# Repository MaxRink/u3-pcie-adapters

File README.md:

# U.3 PCIe adapters

Passive, PCIe 4.0 adapters for U.3 (SFF-TA-1001) NVMe drives, built around HPE P50230-B21 /
Samsung PM1735a drives that refuse U.2-wired hosts. KiCad projects, fabbed at JLCPCB or PCBWay.

## Designs

| Design | Boards | Status |
| --- | --- | --- |
| [**x16 / x8 U.3 cards**](designs/x16-u3-card/) | x8 card (2 drives), x16 card (4 drives, passive or with retimer), OCuLink cage board | cage board routed and DRC clean; cards in layout |
| [**Minisforum MS-01 / MS-A2**](designs/minisforum-u3/) | U.3-wired x4 card for the PCIe slot, U.3-wired replacement for the M.2 adapter | waiting on measurements of the stock adapters |
| [**Cooling shroud**](docs/thermal/) | 3D-printed high-temp shroud for the Jonsbo N5 | sized from the thermal analysis; model in progress |

<table>
<tr>
<td><br>Cage board, top</td>
<td><br>Cage board, bottom (OCuLink)</td>
</tr>
<tr>
<td><br>x8 card with 2 drives</td>
<td><br>x16 card with 4 drives</td>
</tr>
<tr>
<td><br>CFD: 4 drives x 25 W in line, 30 CFM</td>
<td><br>Hottest drive vs airflow (x8 / x16)</td>
</tr>
</table>

## Cooling in one paragraph

Each drive can draw ~25 W, and on the cards the drives sit in a row, so the air passes them one
after another. With 35 °C air coming in and a 70 °C case limit, the x8 card (2 drives) needs about
20 CFM and the x16 card (4 drives) about 30 CFM at ~150 Pa. That takes a 92x38 mm server-class
fan: it holds 2 drives at ~66 °C and 4 drives at ~71 °C (marginal; 3 mm shroud gaps or a 20 W
drive power state give margin). A 92x25 mm fan is not enough for either. Details, OpenFOAM
results and the calibrated model: [`docs/thermal/`](docs/thermal/).

## Layout

| Path | Contents |
| --- | --- |
| [`design-rules/`](design-rules/) | Shared PCIe 4.0 + JLCPCB/PCBWay rules: stackups, impedance, `.kicad_dru` DRC rules, KiCad starter templates, SI scripts |
| [`designs/x16-u3-card/`](designs/x16-u3-card/) | x16 / x8 slot cards for 2–4 U.3 drives, OCuLink cage board |
| [`designs/minisforum-u3/`](designs/minisforum-u3/) | U.3 adapters for Minisforum MS-01 / MS-A2 (PCIe x4 card, M.2-slot board) |
| [`tools/render/`](tools/render/) | Headless 3D renders of any `.kicad_pcb` (real copper/mask/silk, STEP parts, drives plugged in) |
| [`tools/thermal/`](tools/thermal/) | Analytical airflow/thermal model and OpenFOAM CFD case generator for the drive stack |
| [`docs/`](docs/) | Research notes, renders (`docs/img/`), thermal results (`docs/thermal/`) |

## Conventions

- One folder per design under `designs/`; one KiCad project per board inside it.
- Every board uses a template from `design-rules/templates/` and the custom rules in
  `design-rules/pcie4_jlc_pcbway.kicad_dru`. Change the rules there, not per board.
- Don't commit KiCad backups, `*.kicad_prl`, or fab output zips (see `.gitignore`);
  attach fab outputs to GitHub releases instead.
- Re-render a board after changing it (`tools/render/render.py`) so the README pictures match.

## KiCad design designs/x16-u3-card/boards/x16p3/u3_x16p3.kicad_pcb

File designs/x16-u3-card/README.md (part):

# U.3 adapter boards: x16 card, x8 card, OCuLink cage board

Passive PCIe 4.0 boards that carry true SFF-TA-1001 (U.3) wiring to 2.5" U.3 drives such as the
HPE P50230-B21 / Samsung PM1735a, which refuse U.2-wired hosts. Designed for a Jonsbo N5 build
with a 3D-printed cooling shroud.

## Boards

| Board | What it is | Status |
| --- | --- | --- |
| **x8 card** (`boards/x8/`) | x8 slot (x4x4 bifurcation), 2 drives on the card front (CEM component side), passive, REFCLK buffer, full sidebands, per-drive 12 V jumper and eFuse, 191.7 mm with the tail tab for the 6-pin | rev G routed, DRC clean; drive A 28–38 mm, drive B 45–66 mm (three lanes over the 50 mm rule); relies on PCIe lane reversal |
| **x16 card, passive, 4 drives** (`boards/x16p/`) | x16 slot (x4x4x4x4), 4 drives in a row on the card front, 334.7 mm with the tail tab (longer than a full-length CEM card); drives A–C sit 5.7 mm higher than D so lanes 8–15 pass under them | rev G; A 37–46 mm, B 43–69 mm, C ~107–126 mm, D ~158–178 mm: C/D run at PCIe Gen3 (silk says so); relies on lane reversal |
| **x16 card, passive, 3 drives** (`boards/x16p3/`) | same card with drives A–C only, 261.7 mm; host bifurcation x4x4x4 or x8x4x4, lanes 12–15 unused | rev G routed, DRC clean; A 37–46 mm, B 44–69 mm, C 101–121 mm (Gen3) |
| **CDCDB400 clock versions** (`boards/*-cdcdb400/`) | cards with a TI CDCDB400 instead of the PI6CB33401 / 9DBL0442 buffer | x8: rev G. x16: **still rev F (drives on the back)**, not laid out for the front cards yet; see [`docs/part-options.md`](../../docs/part-options.md) |
| **x16 card with retimer** | as above, with a retimer on lanes 8–15 so all 4 drives stay compliant | planned (part search) |
| **OCuLink cage board** (`boards/cage/`) | OCuLink 4i (SFF-8611) to U.3 breakout for a drive in a printed cage; 12 V in on a PCIe 6-pin | rev B routed, DRC clean (review fixes applied; the cabled path still needs a host-card retimer for full compliance) |

Renders are regenerated from the KiCad files whenever a board changes (see
[`tools/render`](../../tools/render/)); boards still in layout get their renders when they are DRC clean.

## OCuLink cage board

Rev B. 56.5 x 37.65 mm, 6 layers (JLC06161H-3313), PCIe lanes on L1/L6 only. The OCuLink receptacle sits on the
bottom in the edge notch, the U.3 receptacle on top mates the drive at the upper edge, and a PCIe 6-pin
(Molex Mini-Fit Jr) brings 12 V through a 3 A PTC fuse; a SOT-89 LDO (MCP1703AT-3302E/MB, pinout checked
against the Microchip datasheet; the HT7533-1 is an LCSC alternative only after its pinout is checked) makes 3.3 V aux. Four M3 slots (3.2 x 6.2 mm, along the insertion axis) hold it in
the printed cage.

Rev B changes (from the rev A review, `docs/reviews/cage-board-review.md`, and `docs/reviews/full-review-2026-11-13.md`):

- 220 nF AC caps on PER0/PER1 (bottom side, L5 voided under the pads). A U.3 drive has no TX caps on lanes 0/1
  (SFF-TA-1001 Rev 1.1 section 4.5), so rev A left those two lanes DC-coupled.
- The drive-side board edge now ends 9.4 mm from the peg line, 0.65 mm short of the housing face, so the board can
  no longer stop the drive before it is fully seated. The receptacle overhangs the edge by design.
- 100 k pull-down on PERST#: a missing or sideband-less cable holds the drive in reset.
- The four low-speed OCuLink vias moved off the PET via row into two rows in front of it, and a return via was
  added between the PET3 and PET2 transitions. The 11 mm slot in the L2/L5 planes is now two short ones with a
  2.7 mm bridge.
- Parts: F1 mSMD300-16V (3 A hold, C6851473), LED KT-0603YG (C2289), C3 50 V (C307331), LDO as above (the AMS1117
  was at its 15 V limit, needs a minimum load and is not stable with ceramic output caps).

The renders below still show rev A.

Still open on this board: the cabled path needs a retimer on the host card for full PCIe 4.0 compliance
(design-rules Rev E), PERST#/REFCLK/SMBus are not isolated when the cage is unpowered, and the PET0 lane is 30.4 mm
(0.4 mm over the per-board target).

| Top | Bottom (seen from below) |
| --- | --- |
|  |  |
|  |  |

With a 15 mm U.3 drive plugged in:

| Front | Back |
| --- | --- |
|  |  |

Copper, mask and silkscreen in the renders come from the real layer geometry. The U.3 and
OCuLink receptacles, the Mini-Fit header and the drive are simplified appearance models.

Fab files: [`fab/cage/`](fab/cage/) (Gerbers, BOM, CPL for JLCPCB / PCBWay).

## Rev G: drives on the card front

From rev G on the U.3 receptacles, the aux power plug, the fan header, the 12 V jumpers and every other tall part
sit on the card front (the CEM component side, where a card may be 14.47 mm tall and more with a free neighbour
slot). The back carries only flat SMD parts. Rev F and earlier had the drives on the back, where a CEM card may
only be 2.67 mm tall; those boards are in the git history (merge of PR #17).

| x8, drives fitted | x16 with 4 drives |
| --- | --- |
|  |  |

**Lane order.** Seen from the front, a receptacle's lane order runs against the finger order. The cards wire every
lane straight through, so finger lane n lands on drive lane 3 - n mod 4, and every x4 port has to train
lane-reversed. Lane reversal is optional in PCIe; most root ports and NVMe controllers do it, but it could not be
confirmed from any document for the EPYC 7002/7003 + Supermicro H12SSL + Samsung PM1735 combination this was
built for. **If neither end reverses, the drive does not link at all.** Check this with one drive before
populating the rest:

```
lspci -vv -s <drive's bus address> | grep -E "LnkCap|LnkSta"
# expected: LnkSta: Speed 16GT/s, Width x4   (drives C/D on the x16 cards: 8GT/s is by design)
```

A link at x1 or x2, or no device at all, means the port did not reverse. The rev F cards (drives on the back) are
the wiring that needs no reversal. Uncrossing the lanes on a front card is possible only by looping every lane
bundle around its receptacle (two signal layers, no room to cross): about 35 mm more per drive, which takes even
drive A out of the 50 mm budget. It is not built.

**How the cards are generated.** `gen/x8.py` and `gen/x16.py` build the card in a mirrored frame (drives on the
bottom, as before) and flip the whole board once when saving (`Kit.mirror_all`). Layer names in the generator are
mirrored too (L1 there is the physical L6, L3 the physical L4).

## x8 card

CEM x8 edge (bifurcate the slot x4x4). Two drives on the card front, the card is cut away behind them for airflow.
Drive A is next to the bracket (lanes 0–3, 28–38 mm), drive B at the free end (lanes 4–7, 45–66 mm; PET6, PET7 and
PER7 are over the 50 mm rule and have their own DRU rule, so expect drive B to be the first to drop to Gen3 on a
marginal host). The REFCLK buffer sits at the free end; the slot clock runs there on L4 under the lane field
(106 mm), drive A's pair comes back on the front layer under drive B. The PCIe 6-pin (J5), its bulk cap and TVS sit
on a 22.6 mm tail tab, plug toward the card end. The fan header is at the bracket end. AC caps (220 nF) sit on the
drive-to-host lanes per SFF-TA-1001. Sidebands and 12 V work as described under
[Sidebands and power](#sidebands-and-power). Fab files: [`fab/x8/`](fab/x8/).

## x16 card (passive)

Same construction with four drives in a row (D C B A from the free end, A at the bracket, 73 mm pitch). The 3-drive
card (`U3_DRIVES=3 python3 gen/x16.py`) is the same design without drive D. The drive at the free end sits on the
low peg line, the others 5.7 mm higher, so the lanes to the far drives pass between the fingers and the nearer
receptacles in a 0.9 mm-pitch stack. Lane lengths finger to receptacle: A 37–46 mm, B 43–69 mm, C 101–126 mm,
D 158–178 mm (the DRU documents the over-budget nets). C and D are past the Gen4 loss budget and are meant to run at
PCIe Gen3 (silk: "C/D: PCIe Gen3 only"). With the tail tab for the 6-pin the 4-drive card is 334.7 mm long, 22.6 mm
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
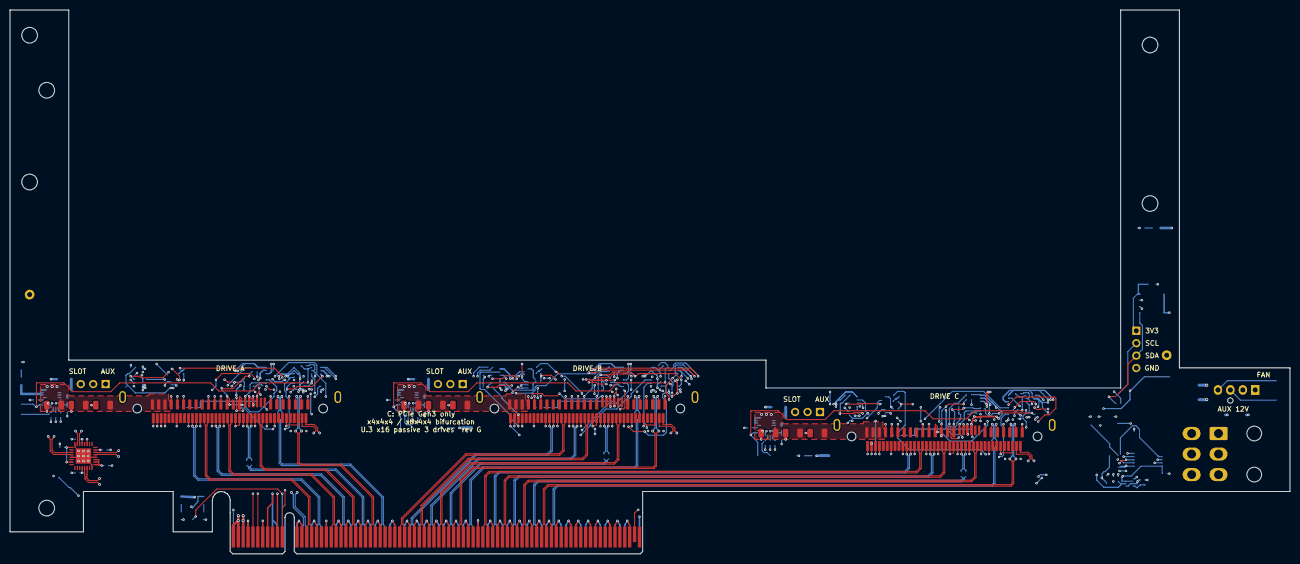
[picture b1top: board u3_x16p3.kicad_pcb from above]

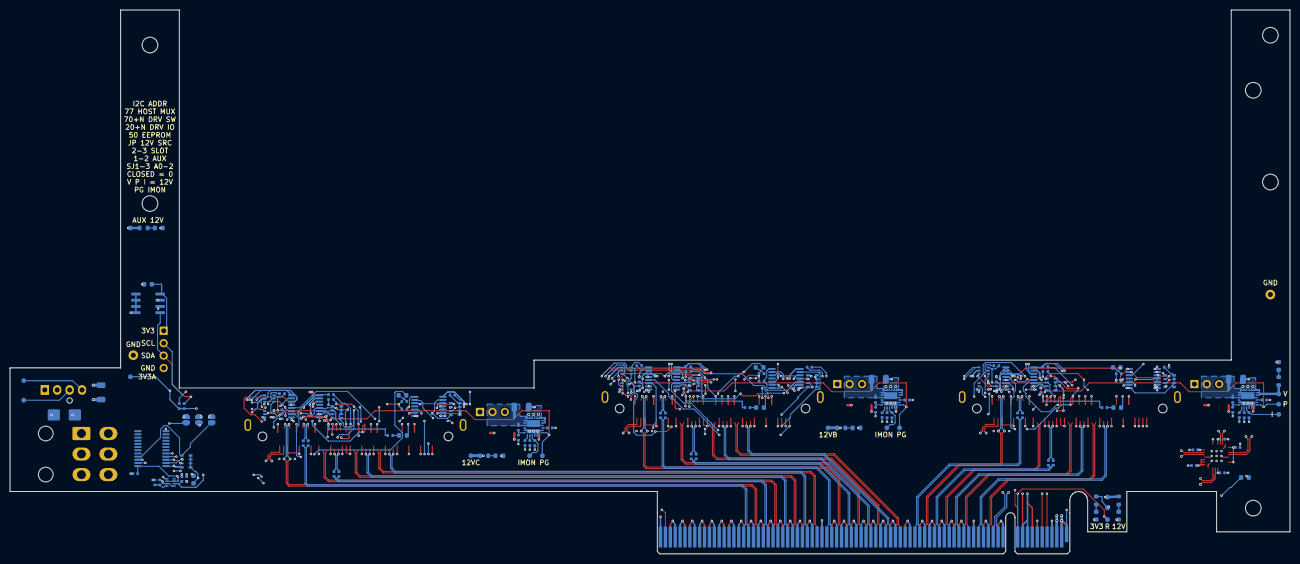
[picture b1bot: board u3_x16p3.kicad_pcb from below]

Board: 6 copper layers, 261.6 x 111.2 mm, 174 parts (152 on the bottom side), 170 nets.

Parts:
C1, C2, C3, C4, C5, C6, C7, C8, C20, C21, C22, C23, C30, C31, C32, C33, C40, C41, C42, C43: 100nF; C_0402_1005Metric
C9: 10uF; C_0603_1608Metric
C19, C24, C25, C34, C35, C44, C45: 22uF 25V X5R; C_1206_3216Metric
C26, C28, C36, C38, C46, C48: 10uF 50V X5R; C_1206_3216Metric
C27, C37, C47: 1nF; C_0402_1005Metric
C29, C39, C49: 4.7nF; C_0402_1005Metric
C90: 100nF; C_0603_1608Metric
C101, C102, C103, C104, C105, C106, C107, C108, C109, C110, C111, C112: 220nF 16V X7R; C_0402_1005Metric
D1, D2, D3, D40, D41, D42, D43, D44, D45: KT-0603YG; LED_0603_1608Metric
D10, D11, D12: XL-1608UYC-06 yellow (locate); LED_0603_1608Metric
D50: SMBJ15A; D_SMB
FB1: 600R@100MHz; L_0603_1608Metric
H1, H2: bracket; MountingHole_3.2mm_M3
H3, H4, H5, H6: M3 slot; MountingSlot_M3_3.2x6.2
H7, H8, H9, H10: M3; MountingHole_3.2mm_M3
J1: PCIe x16 edge; BUS_PCIexpress_x16
J5: PCIe 6-pin 45558-0003; Molex_Mini-Fit_Jr_5569-06A2_2x03_P4.20mm_Horizontal
J6: I2C local bus; PinHeader_1x04_P2.54mm_Vertical
J7: fan 4-pin PWM (fed from the aux 12 V plug); FanPinHeader_1x04_P2.54mm_Vertical
JA: PSAS4F2130021TR; Amphenol_PSAS4F213002_SFF-8639_U3_RA_SMD
JB: PSAS4F2130021TR; Amphenol_PSAS4F213002_SFF-8639_U3_RA_SMD
JC: PSAS4F2130021TR; Amphenol_PSAS4F213002_SFF-8639_U3_RA_SMD
JP1, JP2, JP3: PinHeader 1x03 2.54 mm THT: 2-3 SLOT (default), 1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; PinHeader_1x03_P2.54mm_Vertical
R1, R2: 4.7k; R_0402_1005Metric
R3, R26, R46, R66: 15k; R_0402_1005Metric
R4, R20, R21, R22, R23, R40, R41, R42, R43, R60, R61, R62, R63: 10k; R_0402_1005Metric
R11, R12, R13, R24, R28, R44, R48, R64, R68: 1k; R_0402_1005Metric
R25, R45, R65: 100k; R_0402_1005Metric
R27, R47, R67: 390R; R_0402_1005Metric
R90, R91, R93, R94, R95: 2.2k; R_0603_1608Metric
R92: 1k; R_0603_1608Metric
RN1, RN3, RN5: 4.7k x4; R_Array_Convex_4x0603
RN2, RN4, RN6, RN10: 10k x4; R_Array_Convex_4x0603
SJ1: A0 (close = 0); SolderJumper-2_P1.3mm_Open_RoundedPad1.0x1.5mm
SJ2: A1 (close = 0); SolderJumper-2_P1.3mm_Open_RoundedPad1.0x1.5mm
SJ3: A2 (close = 0); SolderJumper-2_P1.3mm_Open_RoundedPad1.0x1.5mm
TP1: 3V3_AUX; TestPoint_Pad_D1.0mm
TP2: 12V_AUX; TestPoint_Pad_D1.0mm
TP3: 12V; TestPoint_Pad_D1.0mm
TP4: 3V3; TestPoint_Pad_D1.0mm
TP5: PCIE_RST_N; TestPoint_Pad_D1.0mm
TP6: 12V_DRV_C; TestPoint_Pad_D1.0mm
TP7: IMON_C; TestPoint_Pad_D1.0mm
TP8: PG_C; TestPoint_Pad_D1.0mm
TP9: 12V_DRV_B; TestPoint_Pad_D1.0mm
TP10: IMON_B; TestPoint_Pad_D1.0mm
TP11: PG_B; TestPoint_Pad_D1.0mm
TP12: 12V_DRV_A; TestPoint_Pad_D1.0mm
TP13: PG_A; TestPoint_Pad_D1.0mm
TP14: IMON_A; TestPoint_Pad_D1.0mm
TP15: FAN_TACH; TestPoint_Pad_D1.0mm
TP16: FAN_PWM; TestPoint_Pad_D1.0mm
TP90, TP91: GND; TestPoint_Loop_D2.50mm_Drill1.0mm
U1: PI6CB33401ZHIEX; VQFN-32-1EP_5x5mm_P0.5mm_EP3.15x3.15mm
U2: TCA9548APWR; TSSOP-24_4.4x7.8mm_P0.65mm
U3: TPS2116DRLR; SOT-583-8
U4: AT24C02C-SSHM-T; SOIC-8_3.9x4.9mm_P1.27mm
U10, U14, U18: TCA9543APWR; TSSOP-14_4.4x5mm_P0.65mm
U11, U15, U19: TCA9554PWR; TSSOP-16_4.4x5mm_P0.65mm
U12, U16, U20: SN74LVC1G11DCKR; SOT-363_SC-70-6
U13, U17, U21: SN74LVC1G07DCKR; SOT-353_SC-70-5
U30, U31, U32: TPS259824ONRGER; TI_RGE0024M_VQFN-24_4x4mm_P0.5mm_SplitEP

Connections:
3V3: C3.2, C4.2, C5.1, C8.1, FB1.1, J1.A9, J1.A10, J1.B8, R3.2, R92.2, TP4.1, U1.9, U1.10, U1.11, U1.15, U1.19, U1.25, U1.31, U3.3, U3.5
3V3_A: C1.1, C2.1, FB1.2, U1.4, U1.21
3V3_AUX: C6.2, C9.1, C20.2, C21.2, C22.2, C23.1, C30.2, C31.2, C32.2, C33.1, C40.2, C41.2, C42.2, C43.1, C90.2, J6.1, JA.E3, JB.E3, JC.E3, R1.1, R2.1, R11.1, R12.1, R13.1, R21.1, R22.1, R23.1, R24.1, R41.1, R42.1, R43.1, R44.1, R61.1, R62.1, R63.1, R64.1, RN1.5, RN1.6, RN1.7, RN1.8, RN2.5, RN2.6, RN2.7, RN2.8, RN3.5, RN3.6, RN3.7, RN3.8, RN4.5, RN4.6, RN4.7, RN4.8, RN5.5, RN5.6, RN5.7, RN5.8, RN6.5, RN6.6, RN6.7, RN6.8, RN10.5, RN10.6, RN10.7, RN10.8, TP1.1, U2.24, U3.2, U3.7, U4.8, U10.14, U11.16, U12.5, U13.5, U14.1, U14.14, U15.1, U15.16, U16.5, U17.5, U18.2, U18.14, U19.2, U19.16, U20.5, U21.5
3V3_AUX_SLOT: C7.1, J1.B10, U3.6
12V: J1.A2, J1.A3, J1.B1, J1.B2, J1.B3, JP1.3, JP2.3, JP3.3, R91.2, TP3.1
12V_AUX: C19.1, D50.1, J5.1, J5.2, J5.3, J7.2, JP1.1, JP2.1, JP3.1, R90.1, TP2.1
12V_DRV_A: C24.2, C25.2, C26.2, JA.P13, JA.P14, JA.P15, R93.1, TP12.1, U30.17, U30.18, U30.19, U30.20, U30.21, U30.22, U30.23, U30.24
12V_DRV_B: C34.2, C35.2, C36.2, JB.P13, JB.P14, JB.P15, R94.1, TP9.1, U31.17, U31.18, U31.19, U31.20, U31.21, U31.22, U31.23, U31.24
12V_DRV_C: C44.2, C45.2, C46.2, JC.P13, JC.P14, JC.P15, R95.1, TP6.1, U32.17, U32.18, U32.19, U32.20, U32.21, U32.22, U32.23, U32.24
12V_SEL_A: C28.1, JP1.2, R25.2, U30.1, U30.2, U30.3, U30.16, U30.25
12V_SEL_B: C38.1, JP2.2, R45.2, U31.1, U31.2, U31.3, U31.16, U31.25
12V_SEL_C: C48.1, JP3.2, R65.2, U32.1, U32.2, U32.3, U32.16, U32.25
A_ACT_N: D1.1, JA.P11
A_LEDA: D1.2, R11.2
B_ACT_N: D2.1, JB.P11
B_LEDA: D2.2, R12.2
C_ACT_N: D3.1, JC.P11
C_LEDA: D3.2, R13.2
C_PER2_N: C101.2, JA.S12
C_PER2_P: C102.2, JA.S13
C_PER3_N: C103.2, JA.S5
C_PER3_P: C104.2, JA.S6
C_PER6_N: C105.2, JB.S12
C_PER6_P: C106.2, JB.S13
C_PER7_N: C107.2, JB.S5
C_PER7_P: C108.2, JB.S6
C_PER10_N: C109.2, JC.S12
C_PER10_P: C110.2, JC.S13
C_PER11_N: C111.2, JC.S5
C_PER11_P: C112.2, JC.S6
DPEN_A: JA.E25, U11.5
DPEN_B: JB.E25, U15.5
DPEN_C: JC.E25, U19.5
DRST_A: JA.E4, JA.E5, U12.4
DRST_B: JB.E4, JB.E5, U16.4
DRST_C: JC.E4, JC.E5, U20.4
DVDT_A: C27.1, U30.15
DVDT_B: C37.1, U31.15
DVDT_C: C47.1, U32.15
EN_A: R25.1, R26.2, U30.6
EN_B: R45.1, R46.2, U31.6
EN_C: R65.1, R66.2, U32.6
FAN_PWM: J7.4, TP16.1
FAN_TACH: J7.3, TP15.1
GND: C1.2, C2.2, C3.1, C4.1, C5.2, C6.1, C7.2, C8.2, C9.2, C19.2, C20.1, C21.1, C22.1, C23.2, C24.1, C25.1, C26.1, C27.2, C28.2, C29.1, C30.1, C31.1, C32.1, C33.2, C34.1, C35.1, C36.1, C37.2, C38.2, C39.1, C40.1, C41.1, C42.1, C43.2, C44.1, C45.1, C46.1, C47.2, C48.2, C49.1, C90.1, D40.1, D41.1, D42.1, D43.1, D44.1, D45.1, D50.2, J1.A4, J1.A12, J1.A15, J1.A18, J1.A20, J1.A23, J1.A24, J1.A27, J1.A28, J1.A31, J1.A34, J1.A37, J1.A38, J1.A41, J1.A42, J1.A45, J1.A46, J1.A49, J1.A51, J1.A54, J1.A55, J1.A58, J1.A59, J1.A62, J1.A63, J1.A66, J1.A67, J1.A70, J1.A71, J1.A74, J1.A75, J1.A78, J1.A79, J1.A82, J1.B4, J1.B7, J1.B12, J1.B13, J1.B16, J1.B18, J1.B21, J1.B22, J1.B25, J1.B26, J1.B29, J1.B32, J1.B35, J1.B36, J1.B39, J1.B40, J1.B43, J1.B44, J1.B47, J1.B49, J1.B52, J1.B53, J1.B56, J1.B57, J1.B60, J1.B61, J1.B64, J1.B65, J1.B68, J1.B69, J1.B72, J1.B73, J1.B76, J1.B77, J1.B80, J5.4, J5.5, J5.6, J6.4, J7.1, JA.E9, JA.E12, JA.E15, JA.E19, JA.E22, JA.MP, JA.P5, JA.P6, JA.P12, JA.S1, JA.S4, JA.S7, JA.S8, JA.S11, JA.S14, JA.S15, JA.S16, JA.S19, JA.S22, JA.S25, JA.S28, JB.E9, JB.E12, JB.E15, JB.E19, JB.E22, JB.MP, JB.P5, JB.P6, JB.P12, JB.S1, JB.S4, JB.S7, JB.S8, JB.S11, JB.S14, JB.S15, JB.S16, JB.S19, JB.S22, JB.S25, JB.S28, JC.E9, JC.E12, JC.E15, JC.E19, JC.E22, JC.MP, JC.P5, JC.P6, JC.P12, JC.S1, JC.S4, JC.S7, JC.S8, JC.S11, JC.S14, JC.S15, JC.S16, JC.S19, JC.S22, JC.S25, JC.S28, R4.2, R20.1, R26.1, R27.1, R28.1, R40.1, R46.1, R47.1, R48.1, R60.1, R66.1, R67.1, R68.1, SJ1.2, SJ2.2, SJ3.2, TP90.1, TP91.1, U1.8, U1.12, U1.24, U1.29, U1.33, U2.12, U3.1, U4.1, U4.2, U4.3, U4.4, U4.7, U10.1, U10.2, U10.7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
IFDET2_A: JA.E6, RN2.2, U11.11
IFDET2_B: JB.E6, RN4.2, U15.11
IFDET2_C: JC.E6, RN6.2, U19.11
IFDET_A: JA.P4, RN2.3, U11.10
IFDET_B: JB.P4, RN4.3, U15.10
IFDET_C: JC.P4, RN6.3, U19.10
ILIM_A: R27.2, U30.8
ILIM_B: R47.2, U31.8
ILIM_C: R67.2, U32.8
IMON_A: R28.2, TP14.1, U30.9
IMON_B: R48.2, TP10.1, U31.9
IMON_C: R68.2, TP7.1, U32.9
ITIMER_A: C29.2, U30.7
ITIMER_B: C39.2, U31.7
ITIMER_C: C49.2, U32.7
LEDA_3V3: D42.2, R92.1
LEDA_AUX: D40.2, R90.2
LEDA_DRV_A: D43.2, R93.2
LEDA_DRV_B: D44.2, R94.2
LEDA_DRV_C: D45.2, R95.2
LEDA_SLOT: D41.2, R91.1
LOCA_A: D10.2, R24.2
LOCA_B: D11.2, R44.2
LOCA_C: D12.2, R64.2
LOC_A: D10.1, U11.7
LOC_B: D11.1, U15.7
LOC_C: D12.1, U19.7
MUXA0: RN10.4, SJ1.1, U2.1
MUXA1: RN10.2, SJ2.1, U2.2
MUXA2: RN10.1, SJ3.1, U2.21
MUXCTL_A: R23.2, U10.3, U10.4, U10.8
MUXCTL_B: R43.2, U14.3, U14.4, U14.8
MUXCTL_C: R63.2, U18.3, U18.4, U18.8
MUX_RST_N: RN10.3, U2.3
PCIE_RST_N: J1.A11, TP5.1, U12.1, U16.1, U20.1
PCIE_WAKE_N: J1.B11, U13.4, U17.4, U21.4
PER0_N: J1.A17, JA.S26
PER0_P: J1.A16, JA.S27
PER1_N: J1.A22, JA.S20
PER1_P: J1.A21, JA.S21
PER2_N: C101.1, J1.A26
PER2_P: C102.1, J1.A25
PER3_N: C103.1, J1.A30
PER3_P: C104.1, J1.A29
PER4_N: J1.A36, JB.S26
PER4_P: J1.A35, JB.S27
PER5_N: J1.A40, JB.S20
PER5_P: J1.A39, JB.S21
PER6_N: C105.1, J1.A44
PER6_P: C106.1, J1.A43
PER7_N: C107.1, J1.A48
PER7_P: C108.1, J1.A47
PER8_N: J1.A53, JC.S26
PER8_P: J1.A52, JC.S27
PER9_N: J1.A57, JC.S20
PER9_P: J1.A56, JC.S21
PER10_N: C109.1, J1.A61
PER10_P: C110.1, J1.A60
PER11_N: C111.1, J1.A65
PER11_P: C112.1, J1.A64
PET0_N: J1.B15, JA.S23
PET0_P: J1.B14, JA.S24
PET1_N: J1.B20, JA.S17
PET1_P: J1.B19, JA.S18
PET2_N: J1.B24, JA.S9
PET2_P: J1.B23, JA.S10
PET3_N: J1.B28, JA.S2
PET3_P: J1.B27, JA.S3
PET4_N: J1.B34, JB.S23
PET4_P: J1.B33, JB.S24
PET5_N: J1.B38, JB.S17
PET5_P: J1.B37, JB.S18
PET6_N: J1.B42, JB.S9
PET6_P: J1.B41, JB.S10
PET7_N: J1.B46, JB.S2
PET7_P: J1.B45, JB.S3
PET8_N: J1.B51, JC.S23
PET8_P: J1.B50, JC.S24
PET9_N: J1.B55, JC.S17
PET9_P: J1.B54, JC.S18
PET10_N: J1.B59, JC.S9
PET10_P: J1.B58, JC.S10
PET11_N: J1.B63, JC.S2
PET11_P: J1.B62, JC.S3
PG_A: R22.2, TP13.1, U12.6, U30.13
PG_B: R42.2, TP11.1, U16.6, U31.13
PG_C: R62.2, TP8.1, U20.6, U32.13
PR1: R3.1, R4.1, U3.4
PRSNT_A: JA.P10, RN2.4, U11.9
PRSNT_B: JB.P10, RN4.4, U15.9
PRSNT_C: JC.P10, RN6.4, U19.9
PRSNT_N: J1.A1, J1.B81
PWRDIS_A: JA.P3, R20.2, U11.4
PWRDIS_B: JB.P3, R40.2, U15.4
PWRDIS_C: JC.P3, R60.2, U19.4
REFCLK_A_N: JA.E8, U1.28
REFCLK_A_P: JA.E7, U1.27
REFCLK_B_N: JB.E8, U1.23
REFCLK_B_P: JB.E7, U1.22
REFCLK_C_N: JC.E8, U1.14
REFCLK_C_P: JC.E7, U1.13
REFCLK_IN_N: J1.A14, U1.6
REFCLK_IN_P: J1.A13, U1.5
RSTEN_A: R21.2, U11.6, U12.3
RSTEN_B: R41.2, U15.6, U16.3
RSTEN_C: R61.2, U19.6, U20.3
SC1_A: RN1.1, U10.10
SC1_B: RN3.1, U14.10
SC1_C: RN5.1, U18.10
SD1_A: RN1.2, U10.9
SD1_B: RN3.2, U14.9
SD1_C: RN5.2, U18.9
SMBCLK_A: JA.E23, RN1.4, U10.6
SMBCLK_B: JB.E23, RN3.4, U14.6
SMBCLK_C: JC.E23, RN5.4, U18.6
SMBDAT_A: JA.E24, RN1.3, U10.5
SMBDAT_B: JB.E24, RN3.3, U14.5
SMBDAT_C: JC.E24, RN5.3, U18.5
SMCLK: J6.2, R1.2, U2.5, U4.6, U10.12, U11.14, U14.12, U15.14, U18.12, U19.14
SMCLK_SLOT: J1.B5, U2.22
SMDAT: J6.3, R2.2, U2.4, U4.5, U10.13, U11.15, U14.13, U15.15, U18.13, U19.15
SMDAT_SLOT: J1.B6, U2.23
WAKE_A: JA.P1, RN2.1, U11.12, U13.2
WAKE_B: JB.P1, RN4.1, U15.12, U17.2
WAKE_C: JC.P1, RN6.1, U19.12, U21.2

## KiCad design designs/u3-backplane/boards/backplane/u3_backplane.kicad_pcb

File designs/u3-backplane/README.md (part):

# Cabled U.3 backplane

A small NVMe backplane in the style of a Supermicro CSE-SAS-733TQ: U.3 drives stand on vertical receptacles,
every cable leaves sideways on the underside, and a host card in a PCIe x16 slot feeds it over SlimSAS 8i cables.
It is meant to sit flat in the top compartment of a Jonsbo N5 behind the two front 120 mm fans, with the drives
loaded from the top (so they can be swapped with the lid off), inside a printed cage.

| Board | Size | Drives | Cables | Files |
| --- | --- | --- | --- | --- |
| Backplane, 4 drives | 79.6 x 90.5 mm | 4 | 2 x SlimSAS 8i | `boards/backplane`, `fab/backplane` |
| Backplane, 6 drives | 119.6 x 90.5 mm (one 120 mm fan wide) | 6 | 3 x SlimSAS 8i | `boards/backplane6`, `fab/backplane6` |
| Host card, passive | 131 x 44 mm, PCIe x16 | 4 per card | 2 x SlimSAS 8i | `boards/host_passive`, `fab/host_passive` |

Two 6-drive modules side by side give 12 drives across both fans. That is 48 lanes: six 8i cables and three
x16 slots set to x4x4x4x4 (or a PCIe switch card).

All boards use the project's 6-layer rule set (JLC06161H-3313, 85 ohm pairs 0.157 / 0.152 mm, see
`design-rules/`). They are generated by the scripts in `gen/`; nothing is drawn by hand.

## Mechanics

Drawings: `docs/backplane_mech.svg`, `docs/backplane6_mech.svg`. Board-only STEP models are in `fab/*/`.

- Frame: seen from the drive side, origin top-left, x right, y down.
- Drive receptacles (Amphenol PSAS5F3130021TR, vertical, 8.15 mm tall) at x = 9.8 + 20 * i, y = 48.5, long axis
  along y, 20 mm pitch. Module pitch is 80 / 120 mm with 0.4 mm between boards.
- M3 holes: (3.2, 15.5), (W - 3.2, 15.5) and (36 + 40 * c, 86.3) for every drive pair c.
- Underside (all right angle, tallest part 13 mm, the cage keeps 15 mm clear):
  - y = 90.5 edge: one SlimSAS 8i per drive pair, centred at x = 15.8 + 40 * c.
  - y = 0 edge, left to right from the drive side: fan control in (1x4), 12 V in, 12 V out (Mini-Fit Jr 2x4),
    fan + fan control out (1x8).
- Slots between the drives let air through when the board stands upright. Lying flat they are not needed.

Assumed, not measured: the N5 top compartment has room for the cage (Max: "plenty of space"), and the drive's end
face sits about 6.5 mm above the board. The Amphenol drawing gives the 8.15 mm body height only.

## Electrical design

**Lanes.** One x4 link per drive, no lane crossings and exactly one via per net. Host transmit (PET) runs on L1
and drops to L6 behind the SlimSAS pads, drive transmit (PER) runs on L6. Lanes are 19 to 43 mm long. Pairs are
matched by the position of their vias, without serpentines (largest skew 0.004 mm, see
`fab/*/*-lengths.json`). 220 nF AC caps sit on the drive's lane 0 and 1 transmit pairs only
(SFF-TA-1001), S15 (HPT0) is grounded.

| SlimSAS connector | Port A (pins 1-18, host lanes 0-3) | Port B (pins 19-37, host lanes 4-7) |
| --- | --- | --- |
| first (left) | drive 1 | drive 0 |
| second | drive 3 | drive 2 |
| third (6-drive board) | drive 5 | drive 4 |

Sidebands follow SFF-9402: every port carries its own REFCLK, PERST#, CPRSNT#, CWAKE# and BP_TYPE (pulled low).
Cables must be the crossover type the spec describes (row A at one end is row B at the other).

**Power and hot plug.** 12 V enters on a PCIe 8-pin (Mini-Fit Jr) and is passed on to a second one for the next
module. Each drive has its own TPS259824 eFuse: about 3.9 A limit, soft start (10 nF on dV/dt), and it is only
switched on while a drive is present (PRSNT# or IfDet# low through a 74LVC1G00). A TPS3808 watches the drive's
12 V and releases the drive's PERST# about 125 ms after the rail is good, so a freshly inserted drive always sees
a proper reset. An empty bay is unpowered.

Daisy chain limit: a PCIe 8-pin is specified for 150 W. Four 25 W drives are 100 W, six are 150 W, so chain two
4-drive modules only with drives that stay under about 18 W each, and give every 6-drive module its own lead.

Host side of hot plug: the backplane is electrically safe to plug and pull. Whether the OS notices on its own
depends on the root port. A bifurcated consumer slot normally has no hot-plug slot capability, so use
`echo 1 > /sys/bus/pci/devices/<bdf>/remove` before pulling and `echo 1 > /sys/bus/pci/rescan` after inserting.
Boards that expose "PCIe hot plug" or Intel VMD for the slot handle it without that.

**Management.** One TCA9548A SMBus switch (address 0x71) gives every drive its own channel (channel = drive
number). One TCA9554 per drive pair (0x20, 0x21, 0x22) reads PRSNT#, IfDet#, IfDet2# and drives PWRDIS for both
drives (bits 0-3 even drive, 4-7 odd drive). The upstream bus is the 2-wire pair of port A on the first SlimSAS
connector; that port's PERST# also resets the switch. 3.3 V comes from an on-board LDO fed from 12 V (drive side,
above the fan header). L4 carries 12 V above the drives and to every eFuse and 3.3 V everywhere else.

**Fan.** The 1x8 header's pins 1-4 are a standard 4-pin fan header (GND, 12 V through a 1.1 A PTC, tach, PWM).
PWM and tach come from the "control in" header (mainboard fan header or the previous module), and PWM is passed
on by pins 5-8 to the next module. The 12 V pins of the control headers are not connected, so nothing is fed back
into the mainboard.

## Host card (passive)

PCIe x16 edge to two SlimSAS 8i, for a slot set to x4x4x4x4. The connectors sit on the underside at the top edge,
which keeps the lane order of the fingers. PET has one via, PER two. A 9DBL0442 buffer (bypass mode) gives each
port its own REFCLK, a TCA9546A (0x77) gives each port its own SMBus channel (channel 0 reaches the backplane's
switch), a TCA9554 (0x27) reads CPRSNT# and BP_TYPE of the four ports, PERST# goes to every port through 33 ohm
and the four CWAKE# lines join WAKE#. Trace length is 23 to 30 mm per lane.

A passive card plus a 0.5 m cable plus the backplane (19 to 43 mm) is past what PCIe 4.0 allows without
re-equalisation. Expect Gen3 to work and Gen4 to depend on the board and the cable. For Gen4, use a redriver or
retimer card.

**Redriver and retimer versions: not built (decided 2026-11-13).** For PCIe 4.0 a retimer card is bought instead
(see below). A redriver card (4 x DS160PR810) was analysed but not laid out: it does not re-time, so Gen4 over
0.5 m would stay uncertain. A retimer card cannot be laid out from public data, TI's public DS160PT801 datasheet
has no ball map.

## What to buy

Cables (one per drive pair): SlimSAS SFF-8654 8i to 8i, straight, 85 ohm, "PCIe 4.0", with sidebands, 0.5 m or
shorter.

| Cable | Notes |
| --- | --- |
| 3M 8ES8-1DF21-0.50 | reference-grade twinax, 85 ohm; the safest choice |
| 10Gtek CAB-8654/8654-8i-P-85 | "PCIe 4.0, 85 ohm, with sideband", 0.5 to 1 m, listed at about 15 USD (2026-11-13) |
| Delock 82303 (0.5 m) | SlimSAS 8i to 8i; impedance and sidebands not confirmed from the product page |

Avoid 100 ohm "SAS" cables and cables without sidebands: the drives would get no clock or reset.

Host card to buy instead of building one: a x16 to dual SlimSAS 8i **retimer** card, for example LR-LINK
LRNV9F24 or the C-Payne "SlimSAS PCIe gen4 host adapter x16" in its retimer version. Prices could not be read
from the vendor pages (LR-LINK sells on inquiry). Check before ordering that the card follows SFF-9402 on the
cable side (REFCLK and PERST# on every port); a card that only passes lanes will not bring up the drives.

## Cost estimate (JLCPCB, bare boards)

Not quoted live. Scaled from the project's quotes of 2026-11-13 for the same stackup (6 layers, ENIG, impedance
control, 0.2 mm vias: 141 to 188 USD for 5 to 10 cards of 190 to 310 mm length), where the fixed 6-layer charges
dominate:

| Board | 5 pcs | 10 pcs |
| --- | --- | --- |
| Backplane, 4 drives | about 105 USD | about 115 USD |
| Backplane, 6 drives | about 115 USD | about 130 USD |
| Host card (adds gold fingers and bevel) | about 125 USD | about 140 USD |

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
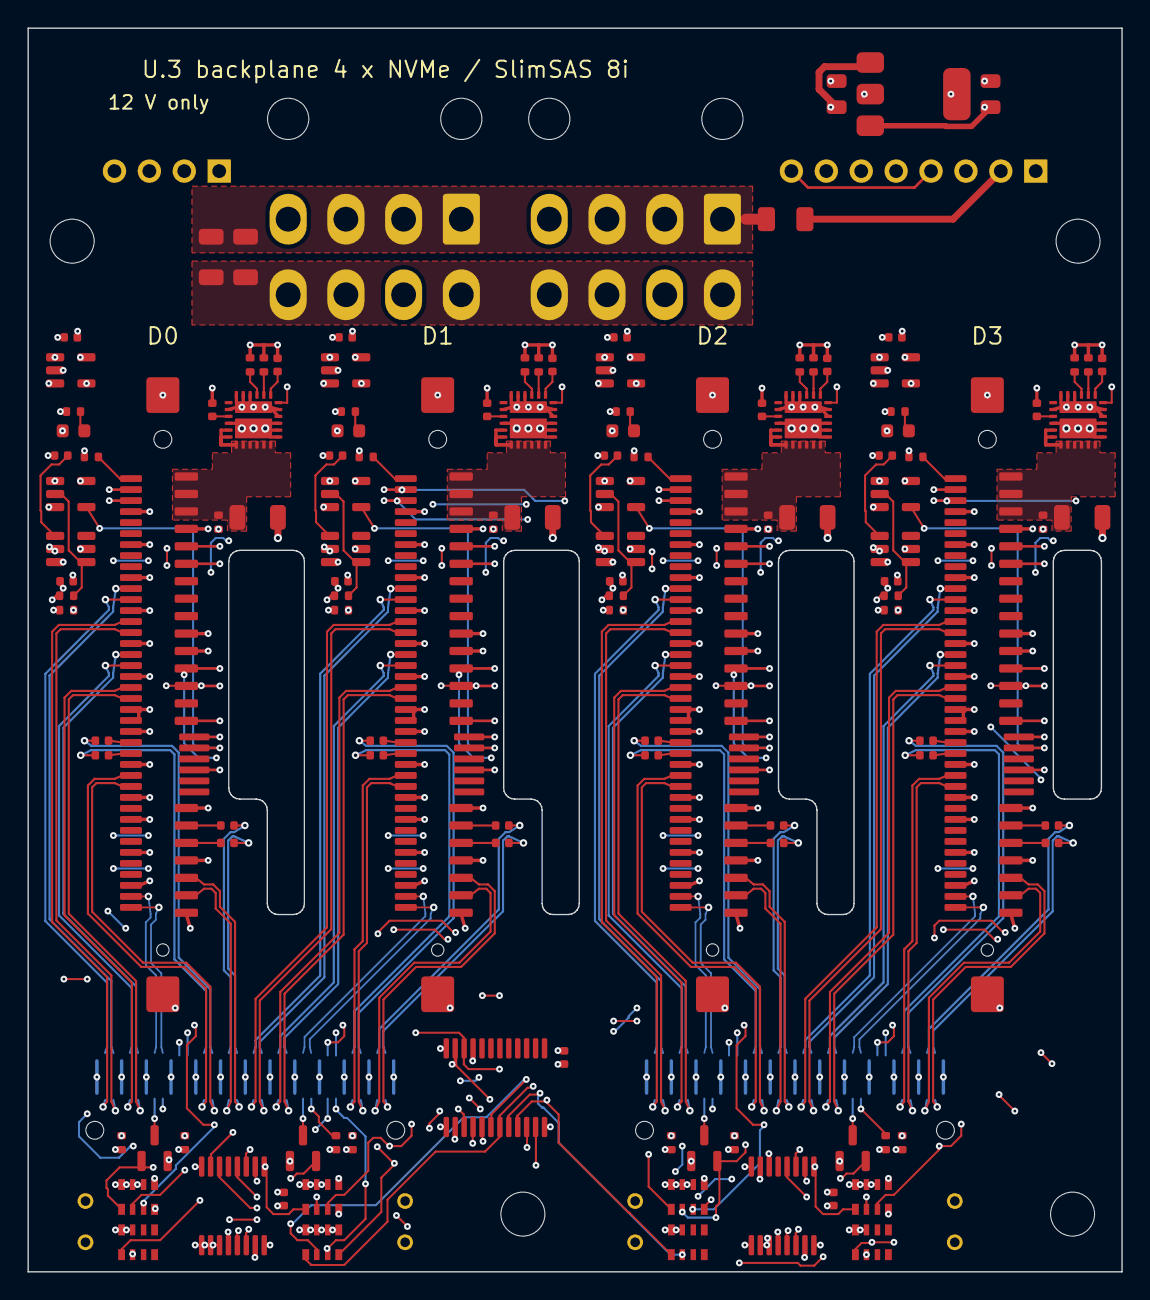
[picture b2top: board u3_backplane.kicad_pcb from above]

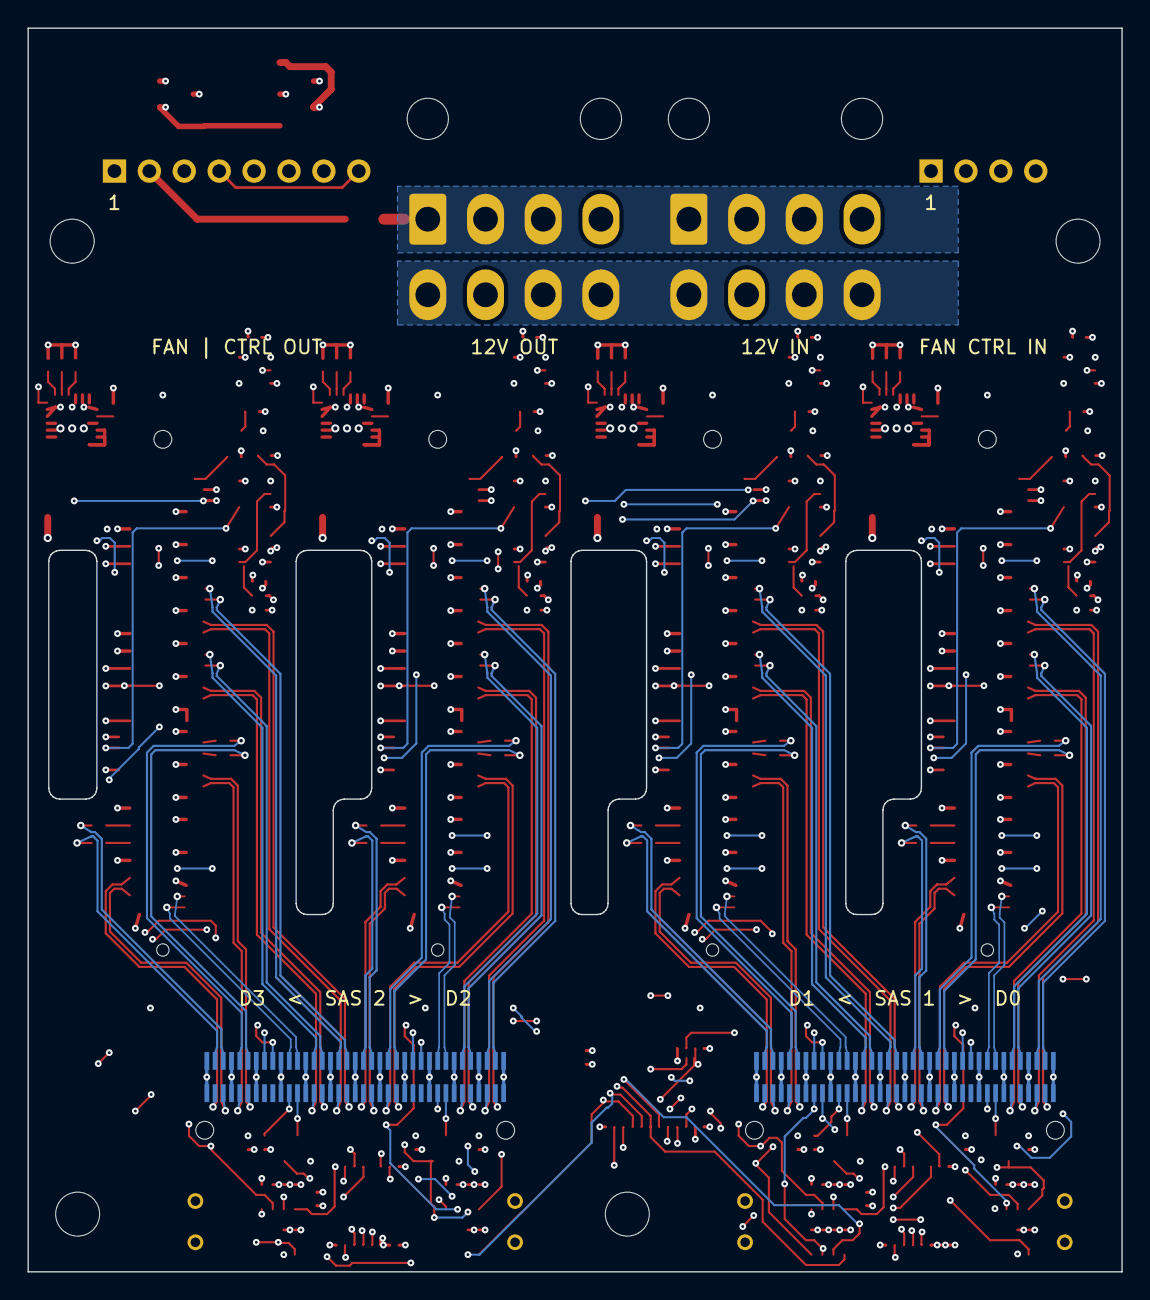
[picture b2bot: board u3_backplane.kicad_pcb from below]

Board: 6 copper layers, 79.6 x 90.5 mm, 134 parts (6 on the bottom side), 188 nets.

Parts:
C1, C2: 10uF 25V X5R; C_0805_2012Metric
C3, C10, C11, C121, C123, C221, C223, C321, C323, C421, C423: 100nF; C_0402_1005Metric
C5, C6, C120, C220, C320, C420: 22uF 25V X5R; C_1206_3216Metric
C101, C102, C111, C112, C201, C202, C211, C212, C301, C302, C311, C312, C401, C402, C411, C412: 220nF; C_0402_1005Metric
C122, C222, C322, C422: 22nF; C_0402_1005Metric
C124, C224, C324, C424: 2.2nF; C_0402_1005Metric
C125, C225, C325, C425: 10nF; C_0402_1005Metric
D1, D2, D3, D4: LED green 0603; LED_0603_1608Metric
D10, D20, D30, D40: BAT54A; SOT-23
F1: PTC 1206 1.1A 16V; Fuse_1206_3216Metric
H1, H2, H3, H4: M3; MountingHole_3.2mm_M3
J1, J2, J3, J4: PSAS5F3130021TR; Amphenol_PSAS5F313002_SFF-8639_U3_Vertical_SMD
J5, J6: U10A474240T; Amphenol_U10A474_SlimSAS_8i_SFF-8654_RA_SMD
J7: 12V IN PCIe 8-pin (Mini-Fit Jr 5569-08A2); Molex_Mini-Fit_Jr_5569-08A2_2x04_P4.20mm_Horizontal
J8: 12V OUT daisy chain (Mini-Fit Jr 5569-08A2); Molex_Mini-Fit_Jr_5569-08A2_2x04_P4.20mm_Horizontal
J9: FAN CTRL IN (from mainboard / previous module); PinHeader_1x04_P2.54mm_Horizontal
J10: FAN (pins 1-4) + FAN CTRL OUT (pins 5-8); PinHeader_1x08_P2.54mm_Horizontal
R11, R21, R31, R41: 24k 1%; R_0402_1005Metric
R12, R22, R32, R42: 1k 1%; R_0402_1005Metric
R13, R14, R17, R19, R23, R24, R27, R29, R33, R34, R37, R39, R43, R44, R47, R49: 10k; R_0402_1005Metric
R15, R25, R35, R45: 1k; R_0402_1005Metric
R16, R26, R36, R46: 100k; R_0402_1005Metric
R18, R28, R38, R48: 390R 1%; R_0402_1005Metric
RN1, RN2, RN3, RN4: 10k x4; R_Array_Convex_4x0603
RN11, RN12, RN13, RN14: 4.7k x4; R_Array_Convex_4x0603
U1: TCA9548APWR; TSSOP-24_4.4x7.8mm_P0.65mm
U3: MCP1703AT-3302E/DB; SOT-223-3_TabPin2
U5, U6: TCA9554PWR; TSSOP-16_4.4x5mm_P0.65mm
U11, U21, U31, U41: TPS3808G01DBVR; SOT-23-6
U12, U22, U32, U42: SN74LVC1G08DBVR; SOT-23-5
U13, U23, U33, U43: SN74LVC1G00DBVR; SOT-23-5
U14, U24, U34, U44: TPS259824ONRGER; TI_RGE0024M_VQFN-24_4x4mm_P0.5mm_SplitEP

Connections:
3V3_AUX: C2.1, C3.1, C10.1, C11.1, C121.1, C123.1, C221.1, C223.1, C321.1, C323.1, C421.1, C423.1, J1.E3, J2.E3, J3.E3, J4.E3, R13.1, R14.1, R15.1, R23.1, R24.1, R25.1, R33.1, R34.1, R35.1, R43.1, R44.1, R45.1, RN1.6, RN1.7, RN1.8, RN2.6, RN2.7, RN2.8, RN3.6, RN3.7, RN3.8, RN4.6, RN4.7, RN4.8, RN11.7, RN11.8, RN12.5, RN12.6, RN12.7, RN12.8, RN13.7, RN13.8, RN14.7, RN14.8, U1.1, U1.24, U3.3, U5.16, U6.1, U6.16, U11.6, U12.5, U13.5, U21.6, U22.5, U23.5, U31.6, U32.5, U33.5, U41.6, U42.5, U43.5
12V_IN: C1.1, C5.2, C6.2, F1.1, J7.1, J7.2, J7.3, J8.1, J8.2, J8.3, U3.1, U14.1, U14.2, U14.3, U14.16, U14.25, U24.1, U24.2, U24.3, U24.16, U24.25, U34.1, U34.2, U34.3, U34.16, U34.25, U44.1, U44.2, U44.3, U44.16, U44.25
D0C_PER0_N: C102.1, J1.S5
D0C_PER0_P: C101.1, J1.S6
D0C_PER1_N: C112.2, J1.S12
D0C_PER1_P: C111.2, J1.S13
D0_12V: C120.1, J1.P13, J1.P14, J1.P15, R11.2, U14.17, U14.18, U14.19, U14.20, U14.21, U14.22, U14.23, U14.24
D0_ACT_N: D1.1, J1.P11
D0_BPTYPE: J5.B26, R17.2
D0_CPRSNT_N: D10.3, J5.A30
D0_CT: C122.2, U11.4
D0_DPEN_N: J1.E25, R14.2
D0_DVDT: C125.1, U14.15
D0_EN: U13.4, U14.6
D0_IFDET2_N: J1.E6, RN1.3, U5.6
D0_IFDET_N: D10.2, J1.P4, RN1.2, U5.5, U13.2
D0_ILIM: R18.1, U14.8
D0_IMON: R19.1, U14.9
D0_ITMR: C124.1, U14.7
D0_LEDA: D1.2, R15.2
D0_PER0_N: C102.2, J5.B20
D0_PER0_P: C101.2, J5.B21
D0_PER1_N: C112.1, J5.B24
D0_PER1_P: C111.1, J5.B23
D0_PER2_N: J1.S20, J5.B33
D0_PER2_P: J1.S21, J5.B32
D0_PER3_N: J1.S26, J5.B36
D0_PER3_P: J1.S27, J5.B35
D0_PET0_N: J1.S3, J5.A20
D0_PET0_P: J1.S2, J5.A21
D0_PET1_N: J1.S10, J5.A24
D0_PET1_P: J1.S9, J5.A23
D0_PET2_N: J1.S18, J5.A33
D0_PET2_P: J1.S17, J5.A32
D0_PET3_N: J1.S24, J5.A36
D0_PET3_P: J1.S23, J5.A35
D0_PG: R13.2, U11.1, U12.2
D0_PRSNT_N: D10.1, J1.P10, RN1.1, U5.4, U13.1
D0_PRSTP: J5.A29, R16.2, U12.1
D0_PRST_N: J1.E5, U12.4
D0_PWRDIS: J1.P3, RN1.4, U5.7
D0_REFCLK_N: J1.E8, J5.B30
D0_REFCLK_P: J1.E7, J5.B29
D0_SCL: J1.E23, RN11.1, U1.5
D0_SDA: J1.E24, RN11.2, U1.4
D0_SNS: R11.1, R12.2, U11.5
D0_WAKE_N: J1.P1, J5.B27
D1C_PER0_N: C202.1, J2.S5
D1C_PER0_P: C201.1, J2.S6
D1C_PER1_N: C212.2, J2.S12
D1C_PER1_P: C211.2, J2.S13
D1_12V: C220.1, J2.P13, J2.P14, J2.P15, R21.2, U24.17, U24.18, U24.19, U24.20, U24.21, U24.22, U24.23, U24.24
D1_ACT_N: D2.1, J2.P11
D1_BPTYPE: J5.B8, R27.2
D1_CPRSNT_N: D20.3, J5.A12
D1_CT: C222.2, U21.4
D1_DPEN_N: J2.E25, R24.2
D1_DVDT: C225.1, U24.15
D1_EN: U23.4, U24.6
D1_IFDET2_N: J2.E6, RN2.3, U5.11
D1_IFDET_N: D20.2, J2.P4, RN2.2, U5.10, U23.2
D1_ILIM: R28.1, U24.8
D1_IMON: R29.1, U24.9
D1_ITMR: C224.1, U24.7
D1_LEDA: D2.2, R25.2
D1_PER0_N: C202.2, J5.B2
D1_PER0_P: C201.2, J5.B3
D1_PER1_N: C212.1, J5.B6
D1_PER1_P: C211.1, J5.B5
D1_PER2_N: J2.S20, J5.B15
D1_PER2_P: J2.S21, J5.B14
D1_PER3_N: J2.S26, J5.B18
D1_PER3_P: J2.S27, J5.B17
D1_PET0_N: J2.S3, J5.A2
D1_PET0_P: J2.S2, J5.A3
D1_PET1_N: J2.S10, J5.A6
D1_PET1_P: J2.S9, J5.A5
D1_PET2_N: J2.S18, J5.A15
D1_PET2_P: J2.S17, J5.A14
D1_PET3_N: J2.S24, J5.A18
D1_PET3_P: J2.S23, J5.A17
D1_PG: R23.2, U21.1, U22.2
D1_PRSNT_N: D20.1, J2.P10, RN2.1, U5.9, U23.1
D1_PRSTP: J5.A11, R26.2, U1.3, U22.1
D1_PRST_N: J2.E5, U22.4
D1_PWRDIS: J2.P3, RN2.4, U5.12
D1_REFCLK_N: J2.E8, J5.B12
D1_REFCLK_P: J2.E7, J5.B11
D1_SCL: J2.E23, RN12.1, U1.7
D1_SDA: J2.E24, RN12.2, U1.6
D1_SNS: R21.1, R22.2, U21.5
D1_WAKE_N: J2.P1, J5.B9
D2C_PER0_N: C302.1, J3.S5
D2C_PER0_P: C301.1, J3.S6
D2C_PER1_N: C312.2, J3.S12
D2C_PER1_P: C311.2, J3.S13
D2_12V: C320.1, J3.P13, J3.P14, J3.P15, R31.2, U34.17, U34.18, U34.19, U34.20, U34.21, U34.22, U34.23, U34.24
D2_ACT_N: D3.1, J3.P11
D2_BPTYPE: J6.B26, R37.2
D2_CPRSNT_N: D30.3, J6.A30
D2_CT: C322.2, U31.4
D2_DPEN_N: J3.E25, R34.2
D2_DVDT: C325.1, U34.15
D2_EN: U33.4, U34.6
D2_IFDET2_N: J3.E6, RN3.3, U6.6
D2_IFDET_N: D30.2, J3.P4, RN3.2, U6.5, U33.2
D2_ILIM: R38.1, U34.8
D2_IMON: R39.1, U34.9
D2_ITMR: C324.1, U34.7
D2_LEDA: D3.2, R35.2
D2_PER0_N: C302.2, J6.B20
D2_PER0_P: C301.2, J6.B21
D2_PER1_N: C312.1, J6.B24
D2_PER1_P: C311.1, J6.B23
D2_PER2_N: J3.S20, J6.B33
D2_PER2_P: J3.S21, J6.B32
D2_PER3_N: J3.S26, J6.B36
D2_PER3_P: J3.S27, J6.B35
D2_PET0_N: J3.S3, J6.A20
D2_PET0_P: J3.S2, J6.A21
D2_PET1_N: J3.S10, J6.A24
D2_PET1_P: J3.S9, J6.A23
D2_PET2_N: J3.S18, J6.A33
D2_PET2_P: J3.S17, J6.A32
D2_PET3_N: J3.S24, J6.A36
D2_PET3_P: J3.S23, J6.A35
D2_PG: R33.2, U31.1, U32.2
D2_PRSNT_N: D30.1, J3.P10, RN3.1, U6.4, U33.1
D2_PRSTP: J6.A29, R36.2, U32.1
D2_PRST_N: J3.E5, U32.4
D2_PWRDIS: J3.P3, RN3.4, U6.7
D2_REFCLK_N: J3.E8, J6.B30
D2_REFCLK_P: J3.E7, J6.B29
D2_SCL: J3.E23, RN13.1, U1.9
D2_SDA: J3.E24, RN13.2, U1.8
D2_SNS: R31.1, R32.2, U31.5
D2_WAKE_N: J3.P1, J6.B27
D3C_PER0_N: C402.1, J4.S5
D3C_PER0_P: C401.1, J4.S6
D3C_PER1_N: C412.2, J4.S12
D3C_PER1_P: C411.2, J4.S13
D3_12V: C420.1, J4.P13, J4.P14, J4.P15, R41.2, U44.17, U44.18, U44.19, U44.20, U44.21, U44.22, U44.23, U44.24
D3_ACT_N: D4.1, J4.P11
D3_BPTYPE: J6.B8, R47.2
D3_CPRSNT_N: D40.3, J6.A12
D3_CT: C422.2, U41.4
D3_DPEN_N: J4.E25, R44.2
D3_DVDT: C425.1, U44.15
D3_EN: U43.4, U44.6
D3_IFDET2_N: J4.E6, RN4.3, U6.11
D3_IFDET_N: D40.2, J4.P4, RN4.2, U6.10, U43.2
D3_ILIM: R48.1, U44.8
D3_IMON: R49.1, U44.9
D3_ITMR: C424.1, U44.7
D3_LEDA: D4.2, R45.2
D3_PER0_N: C402.2, J6.B2
D3_PER0_P: C401.2, J6.B3
D3_PER1_N: C412.1, J6.B6
D3_PER1_P: C411.1, J6.B5
D3_PER2_N: J4.S20, J6.B15
D3_PER2_P: J4.S21, J6.B14
D3_PER3_N: J4.S26, J6.B18
D3_PER3_P: J4.S27, J6.B17
D3_PET0_N: J4.S3, J6.A2
D3_PET0_P: J4.S2, J6.A3
D3_PET1_N: J4.S10, J6.A6
D3_PET1_P: J4.S9, J6.A5
D3_PET2_N: J4.S18, J6.A15
D3_PET2_P: J4.S17, J6.A14
D3_PET3_N: J4.S24, J6.A18
D3_PET3_P: J4.S23, J6.A17
D3_PG: R43.2, U41.1, U42.2
D3_PRSNT_N: D40.1, J4.P10, RN4.1, U6.9, U43.1
D3_PRSTP: J6.A11, R46.2, U42.1
D3_PRST_N: J4.E5, U42.4
D3_PWRDIS: J4.P3, RN4.4, U6.12
D3_REFCLK_N: J4.E8, J6.B12
D3_REFCLK_P: J4.E7, J6.B11
D3_SCL: J4.E23, RN14.1, U1.11
D3_SDA: J4.E24, RN14.2, U1.10
D3_SNS: R41.1, R42.2, U41.5
D3_WAKE_N: J4.P1, J6.B9
FAN_12V: F1.2, J10.2
FAN_PWM: J9.4, J10.4, J10.8
FAN_TACH: J9.3, J10.3
GND: C1.2, C2.2, C3.2, C5.1, C6.1, C10.2, C11.2, C120.2, C121.2, C122.1, C123.2, C124.2, C125.2, C220.2, C221.2, C222.1, C223.2, C224.2, C225.2, C320.2, C321.2, C322.1, C323.2, C324.2, C325.2, C420.2, C421.2, C422.1, C423.2, C424.2, C425.2, J1.E9, J1.E12, J1.E15, J1.E19, J1.E22, J1.MP, J1.P5, J1.P6, J1.P12, J1.S1, J1.S4, J1.S7, J1.S8, J1.S11, J1.S14, J1.S15, J1.S16, J1.S19, J1.S22, J1.S25, J1.S28, J2.E9, J2.E12, J2.E15, J2.E19, J2.E22, J2.MP, J2.P5, J2.P6, J2.P12, J2.S1, J2.S4, J2.S7, J2.S8, J2.S11, J2.S14, J2.S15, J2.S16, J2.S19, J2.S22, J2.S25, J2.S28, J3.E9, J3.E12, J3.E15, J3.E19, J3.E22, J3.MP, J3.P5, J3.P6, J3.P12, J3.S1, J3.S4, J3.S7, J3.S8, J3.S11, J3.S14, J3.S15, J3.S16, J3.S19, J3.S22, J3.S25, J3.S28, J4.E9, J4.E12, J4.E15, J4.E19, J4.E22, J4.MP, J4.P5, J4.P6, J4.P12, J4.S1, J4.S4, J4.S7, J4.S8, J4.S11, J4.S14, J4.S15, J4.S16, J4.S19, J4.S22, J4.S25, J4.S28, J5.A1, J5.A4, J5.A7, J5.A10, J5.A13, J5.A16, J5.A19, J5.A22, J5.A25, J5.A28, J5.A31, J5.A34, J5.A37, J5.B1, J5.B4, J5.B7, J5.B10, J5.B13, J5.B16, J5.B19, J5.B22, J5.B25, J5.B28, J5.B31, J5.B34, J5.B37, J5.SH, J6.A1, J6.A4, J6.A7, J6.A10, J6.A13, J6.A16, J6.A19, J6.A22, J6.A25, J6.A28, J6.A31, J6.A34, J6.A37, J6.B1, J6.B4, J6.B7, J6.B10, J6.B13, J6.B16, J6.B19, J6.B22, J6.B25, J6.B28, J6.B31, J6.B34, J6.B37, J6.SH, J7.5, J7.7, J7.8, J8.5, J8.7, J8.8, J9.1, J10.1, J10.5, R12.1, R16.1, R17.1, R18.2, R19.2, R22.1, R26.1, R27.1, R28.2, R29.2, R32.1, R36.1, R37.1, R38.2, R39.2, R42.1, R46.1, R47.1, R48.2, R49.2, RN1.5, RN2.5, RN3.5, RN4.5, U1.2, U1.12, U1.21, U3.2, U5.1, U5.2, U5.3, U5.8, U6.2, U6.3, U6.8, U11.2, U12.3, U13.3, U14.4, U14.5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
HOST_SCL: J5.A8, RN12.3, U1.22, U5.14, U6.14
HOST_SDA: J5.A9, RN12.4, U1.23, U5.15, U6.15
